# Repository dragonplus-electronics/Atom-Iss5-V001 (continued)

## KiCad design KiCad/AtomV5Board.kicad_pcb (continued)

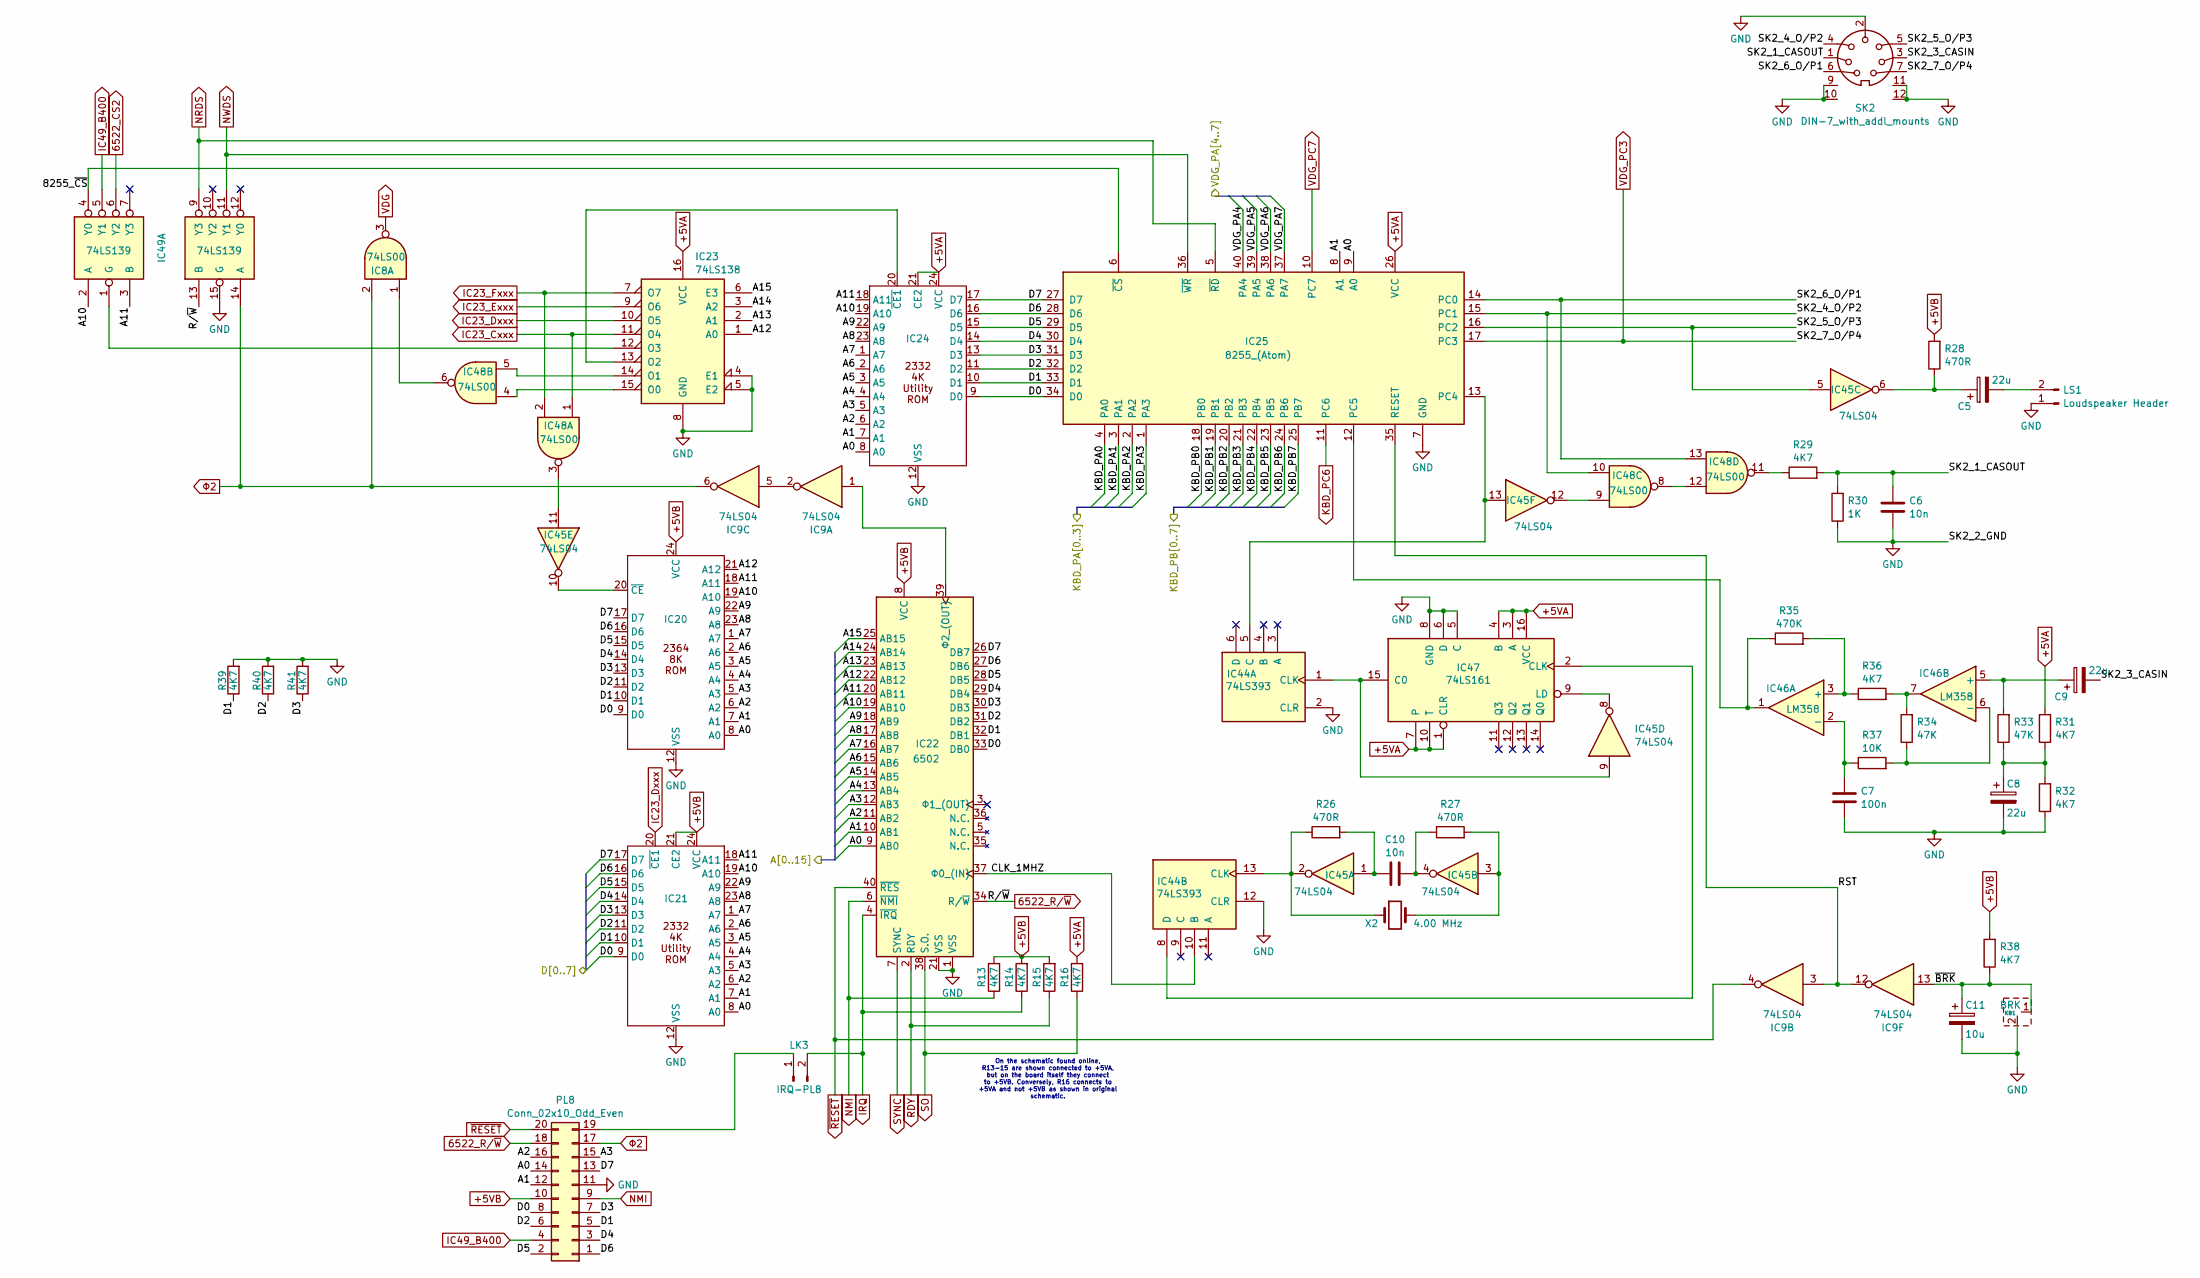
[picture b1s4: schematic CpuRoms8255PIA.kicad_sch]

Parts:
C5: 22u; CP_Radial_LineOnly_P2.54mm_Vertical
C6: 10n; C_Disc_LineOnly_P5.08mm
C7: 100n; C_Disc_LineOnly_P7.62mm
C8: 22u; CP_Axial_LineOnly_P17.78mm_Horizontal
C9: 22u; C_Disc_LineOnly_P5.08mm
C10: 10n; C_Disc_LineOnly_P10.16mm
C11: 10u; CP_Axial_LineOnly_P15.24mm_Horizontal
IC8, IC48: 74LS00; DIP-14_W7.62mm_InnerMarking
IC9, IC45: 74LS04; DIP-14_W7.62mm_InnerMarking
IC20, IC21, IC24: DIP-24_W15.24mm_InnerMarking
IC22: 6502; DIP-40_W15.24mm_InnerMarking
IC23: 74LS138; DIP-16_W7.62mm_InnerMarking
IC25: 8255_(Atom); DIP-40_W15.24mm_InnerMarking
IC44: 74LS393; DIP-14_W7.62mm_InnerMarking
IC46: LM358; DIP-8_W7.62mm_InnerMarking
IC47: 74LS161; DIP-16_W7.62mm_InnerMarking
IC49: 74LS139; DIP-16_W7.62mm_InnerMarking
KB1: BRK; AtomKeyswitch
LK3: IRQ-PL8; PinHeader_1x02_P2.54mm_Vertical
LS1: Loudspeaker Header; PinHeader_1x02_P2.54mm_Vertical
PL8: Conn_02x10_Odd_Even; Atom_IDC-Header_2x10_P2.54mm_Vertical
R13, R14, R15, R16: 4K7; R_Axial_DIN0207_LineOnly_P3.81mm_Vertical
R26, R27, R28: 470R; R_Axial_DIN0207_LineOnly_P2.54mm_Vertical
R29, R39, R40, R41: 4K7; R_Axial_DIN0207_LineOnly_P2.54mm_Vertical
R30: 1K; R_Axial_DIN0207_LineOnly_P2.54mm_Vertical
R31, R32, R36, R38: 4K7; R_Axial_DIN0207_LineOnly_P10.16mm_Horizontal
R33, R34: 47K; R_Axial_DIN0207_LineOnly_P10.16mm_Horizontal
R35: 470K; R_Axial_DIN0207_LineOnly_P10.16mm_Horizontal
R37: 10K; R_Axial_DIN0207_LineOnly_P10.16mm_Horizontal
SK2: DIN-7_with_addl_mounts; DIN-7_RA
X2: 4.00 MHz; C_Disc_LineOnly_P10.16mm

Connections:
6522_CS2: IC49.6 (Y2); also elsewhere on the board
6522_R/~W: IC22.34 (R/~W), IC49.13 (B), PL8.18; also elsewhere on the board
+5VA: IC23.16 (VCC), IC24.21 (CE2), IC24.24 (VCC), IC25.26 (VCC), IC47.1 (CLR), IC47.3 (A), IC47.4 (B), IC47.7, IC47.10 (T), IC47.16 (VCC), R16.2, R31.2; also elsewhere on the board
+5VB: IC20.24 (VCC), IC21.21 (CE2), IC21.24 (VCC), IC22.8 (VCC), PL8.10, R13.2, R14.2, R15.2, R28.2, R38.2; also elsewhere on the board
/6522_PIA & Ports/A0: IC20.8 (A0), IC21.8 (A0), IC22.9 (AB0), IC24.8 (A0), IC25.9 (A0), PL8.14; also elsewhere on the board
/6522_PIA & Ports/A1: IC20.7 (A1), IC21.7 (A1), IC22.10 (AB1), IC24.7 (A1), IC25.8 (A1), PL8.12; also elsewhere on the board
/6522_PIA & Ports/A2: IC20.6 (A2), IC21.6 (A2), IC22.11 (AB2), IC24.6 (A2), PL8.16; also elsewhere on the board
/6522_PIA & Ports/A3: IC20.5 (A3), IC21.5 (A3), IC22.12 (AB3), IC24.5 (A3), PL8.15; also elsewhere on the board
/6522_PIA & Ports/A4: IC20.4 (A4), IC21.4 (A4), IC22.13 (AB4), IC24.4 (A4); also elsewhere on the board
/6522_PIA & Ports/A5: IC20.3 (A5), IC21.3 (A5), IC22.14 (AB5), IC24.3 (A5); also elsewhere on the board
/6522_PIA & Ports/A6: IC20.2 (A6), IC21.2 (A6), IC22.15 (AB6), IC24.2 (A6); also elsewhere on the board
/6522_PIA & Ports/A7: IC20.1 (A7), IC21.1 (A7), IC22.16 (AB7), IC24.1 (A7); also elsewhere on the board
/6522_PIA & Ports/A8: IC20.23 (A8), IC21.23 (A8), IC22.17 (AB8), IC24.23 (A8); also elsewhere on the board
/6522_PIA & Ports/A9: IC20.22 (A9), IC21.22 (A9), IC22.18 (AB9), IC24.22 (A9); also elsewhere on the board
/6522_PIA & Ports/A10: IC20.19 (A10), IC21.19 (A10), IC22.19 (AB10), IC24.19 (A10), IC49.2 (A); also elsewhere on the board
/6522_PIA & Ports/A11: IC20.18 (A11), IC21.18 (A11), IC22.20 (AB11), IC24.18 (A11), IC49.3 (B); also elsewhere on the board
/6522_PIA & Ports/A12: IC20.21 (A12), IC22.22 (AB12), IC23.1 (A0); also elsewhere on the board
/6522_PIA & Ports/A13: IC22.23 (AB13), IC23.2 (A1); also elsewhere on the board
/6522_PIA & Ports/A14: IC22.24 (AB14), IC23.3 (A2); also elsewhere on the board
/6522_PIA & Ports/A15: IC22.25 (AB15), IC23.6 (E3); also elsewhere on the board
/6522_PIA & Ports/D0: IC20.9 (D0), IC21.9 (D0), IC22.33 (DB0), IC24.9 (D0), IC25.34 (D0), PL8.8; also elsewhere on the board
/6522_PIA & Ports/D1: IC20.10 (D1), IC21.10 (D1), IC22.32 (DB1), IC24.10 (D1), IC25.33 (D1), PL8.5, R39.1; also elsewhere on the board
/6522_PIA & Ports/D2: IC20.11 (D2), IC21.11 (D2), IC22.31 (DB2), IC24.11 (D2), IC25.32 (D2), PL8.6, R40.1; also elsewhere on the board
/6522_PIA & Ports/D3: IC20.13 (D3), IC21.13 (D3), IC22.30 (DB3), IC24.13 (D3), IC25.31 (D3), PL8.7, R41.1; also elsewhere on the board
/6522_PIA & Ports/D4: IC20.14 (D4), IC21.14 (D4), IC22.29 (DB4), IC24.14 (D4), IC25.30 (D4), PL8.3; also elsewhere on the board
/6522_PIA & Ports/D5: IC20.15 (D5), IC21.15 (D5), IC22.28 (DB5), IC24.15 (D5), IC25.29 (D5), PL8.2; also elsewhere on the board
/6522_PIA & Ports/D6: IC20.16 (D6), IC21.16 (D6), IC22.27 (DB6), IC24.16 (D6), IC25.28 (D6), PL8.1; also elsewhere on the board
/6522_PIA & Ports/D7: IC20.17 (D7), IC21.17 (D7), IC22.26 (DB7), IC24.17 (D7), IC25.27 (D7), PL8.13; also elsewhere on the board
/CPU, ROMs & 8255 PIA/8255_~CS: IC25.6 (~CS), IC49.4 (Y0)
/CPU, ROMs & 8255 PIA/CLK_1MHZ: IC22.37 (Φ0_(IN)), IC44.10 (B)
/CPU, ROMs & 8255 PIA/KBD_PA0: IC25.4 (PA0); also elsewhere on the board
/CPU, ROMs & 8255 PIA/KBD_PA1: IC25.3 (PA1); also elsewhere on the board
/CPU, ROMs & 8255 PIA/KBD_PA2: IC25.2 (PA2); also elsewhere on the board
/CPU, ROMs & 8255 PIA/KBD_PA3: IC25.1 (PA3); also elsewhere on the board
/CPU, ROMs & 8255 PIA/KBD_PB0: IC25.18 (PB0); also elsewhere on the board
/CPU, ROMs & 8255 PIA/KBD_PB1: IC25.19 (PB1); also elsewhere on the board
/CPU, ROMs & 8255 PIA/KBD_PB2: IC25.20 (PB2); also elsewhere on the board
/CPU, ROMs & 8255 PIA/KBD_PB3: IC25.21 (PB3); also elsewhere on the board
/CPU, ROMs & 8255 PIA/KBD_PB4: IC25.22 (PB4); also elsewhere on the board
/CPU, ROMs & 8255 PIA/KBD_PB5: IC25.23 (PB5); also elsewhere on the board
/CPU, ROMs & 8255 PIA/KBD_PB6: IC25.24 (PB6); also elsewhere on the board
/CPU, ROMs & 8255 PIA/KBD_PB7: IC25.25 (PB7); also elsewhere on the board
/CPU, ROMs & 8255 PIA/RST: IC9.3, IC9.12, IC25.35 (RESET)
/CPU, ROMs & 8255 PIA/SK2_1_CASOUT: C6.1, R29.2, R30.2, SK2.1
/CPU, ROMs & 8255 PIA/SK2_3_CASIN: C9.2, SK2.3
/CPU, ROMs & 8255 PIA/SK2_4_O/P2: IC25.15 (PC1), IC48.10, SK2.4
/CPU, ROMs & 8255 PIA/SK2_5_O/P3: IC25.16 (PC2), IC45.5, SK2.5
/CPU, ROMs & 8255 PIA/SK2_6_O/P1: IC25.14 (PC0), IC48.13, SK2.6
/CPU, ROMs & 8255 PIA/VDG_PA4: IC25.40 (PA4); also elsewhere on the board
/CPU, ROMs & 8255 PIA/VDG_PA5: IC25.39 (PA5); also elsewhere on the board
/CPU, ROMs & 8255 PIA/VDG_PA6: IC25.38 (PA6); also elsewhere on the board
/CPU, ROMs & 8255 PIA/VDG_PA7: IC25.37 (PA7); also elsewhere on the board
/CPU, ROMs & 8255 PIA/~BRK: C11.1, IC9.13, KB1.1, R38.1
GND: C6.2, C7.1, C8.2, C11.2, IC20.12 (VSS), IC21.12 (VSS), IC22.1 (VSS), IC22.21 (VSS), IC23.4 (E1), IC23.5 (E2), IC23.8 (GND), IC24.12 (VSS), IC25.7 (GND), IC44.2 (CLR), IC44.12 (CLR), IC47.5 (C), IC47.6 (D), IC47.8 (GND), IC49.15 (G), KB1.2, LS1.1, PL8.11, R30.1, R32.1, R39.2, R40.2, R41.2, SK2.2, SK2.9, SK2.10, SK2.11, SK2.12; also elsewhere on the board
IC23_Cxxx: IC23.11 (O4), IC48.1
IC23_Dxxx: IC21.20 (~CE1), IC23.10 (O5)
IC23_Exxx: IC23.9 (O6); also elsewhere on the board
IC23_Fxxx: IC23.7 (O7), IC48.2
IC49_B400: IC49.5 (Y1), PL8.4
IRQ: IC22.4 (~IRQ), LK3.2, R14.1; also elsewhere on the board
KBD_PC6: IC25.11 (PC6); also elsewhere on the board
NMI: IC22.6 (~NMI), PL8.9, R13.1; also elsewhere on the board
NRDS: IC25.5 (~RD), IC49.9 (Y3); also elsewhere on the board
NWDS: IC25.36 (~WR), IC49.11 (Y1); also elsewhere on the board
unnamed: C5.1, IC45.6, R28.1
unnamed: C8.1, R31.1, R32.2, R33.1
unnamed: C10.1, IC45.1, R26.2
unnamed: C10.2, IC45.4, R27.1
unnamed: IC9.2, IC9.5
unnamed: IC20.20 (~CE), IC45.10
unnamed: IC9.1, IC22.39 (Φ2_(OUT))
unnamed: IC23.15 (O0), IC48.4
unnamed: IC23.14 (O1), IC48.5
unnamed: IC23.13 (O2), IC24.20 (~CE1)
unnamed: IC23.12 (O3), IC49.1 (G)
unnamed: IC25.13 (PC4), IC44.5 (C), IC45.13
unnamed: IC25.12 (PC5), IC46.1, R35.1
unnamed: IC44.1 (CLK), IC45.9, IC47.15 (C0)
unnamed: IC44.13 (CLK), IC45.2, R26.1, X2.1
unnamed: IC44.8 (D), IC47.2 (CLK)
unnamed: IC45.3, R27.2, X2.2
unnamed: IC45.11, IC48.3
unnamed: IC45.12, IC48.9
unnamed: IC46.7, R34.2, R36.2
unnamed: IC46.3 (+), R35.2, R36.1
unnamed: C7.2, IC46.2 (-), R37.1
unnamed: C9.1, IC46.5 (+), R33.2
unnamed: IC46.6 (-), R34.1, R37.2
unnamed: IC45.8, IC47.9 (LD)
unnamed: IC8.1, IC48.6
unnamed: IC48.11, R29.1
unnamed: IC48.8, IC48.12
unnamed: LK3.1, PL8.19
unnamed: C5.2, LS1.2
RDY: IC22.2 (RDY), R15.1; also elsewhere on the board
SO: IC22.38 (S.O.), R16.1; also elsewhere on the board
SYNC: IC22.7 (SYNC); also elsewhere on the board
VDG: IC8.3; also elsewhere on the board
VDG_PC3: IC25.17 (PC3), SK2.7; also elsewhere on the board
VDG_PC7: IC25.10 (PC7); also elsewhere on the board
~RESET: IC9.4, IC22.40 (~RES), PL8.20; also elsewhere on the board
Φ2: IC8.2, IC9.6, IC49.14 (A), PL8.17; also elsewhere on the board

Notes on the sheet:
On the schematic found online, R13-15 are shown connected to +5VA, but on the board itself they connect to +5VB. Conversely, R16 connects to +5VA and not +5VB as shown in original schematic.

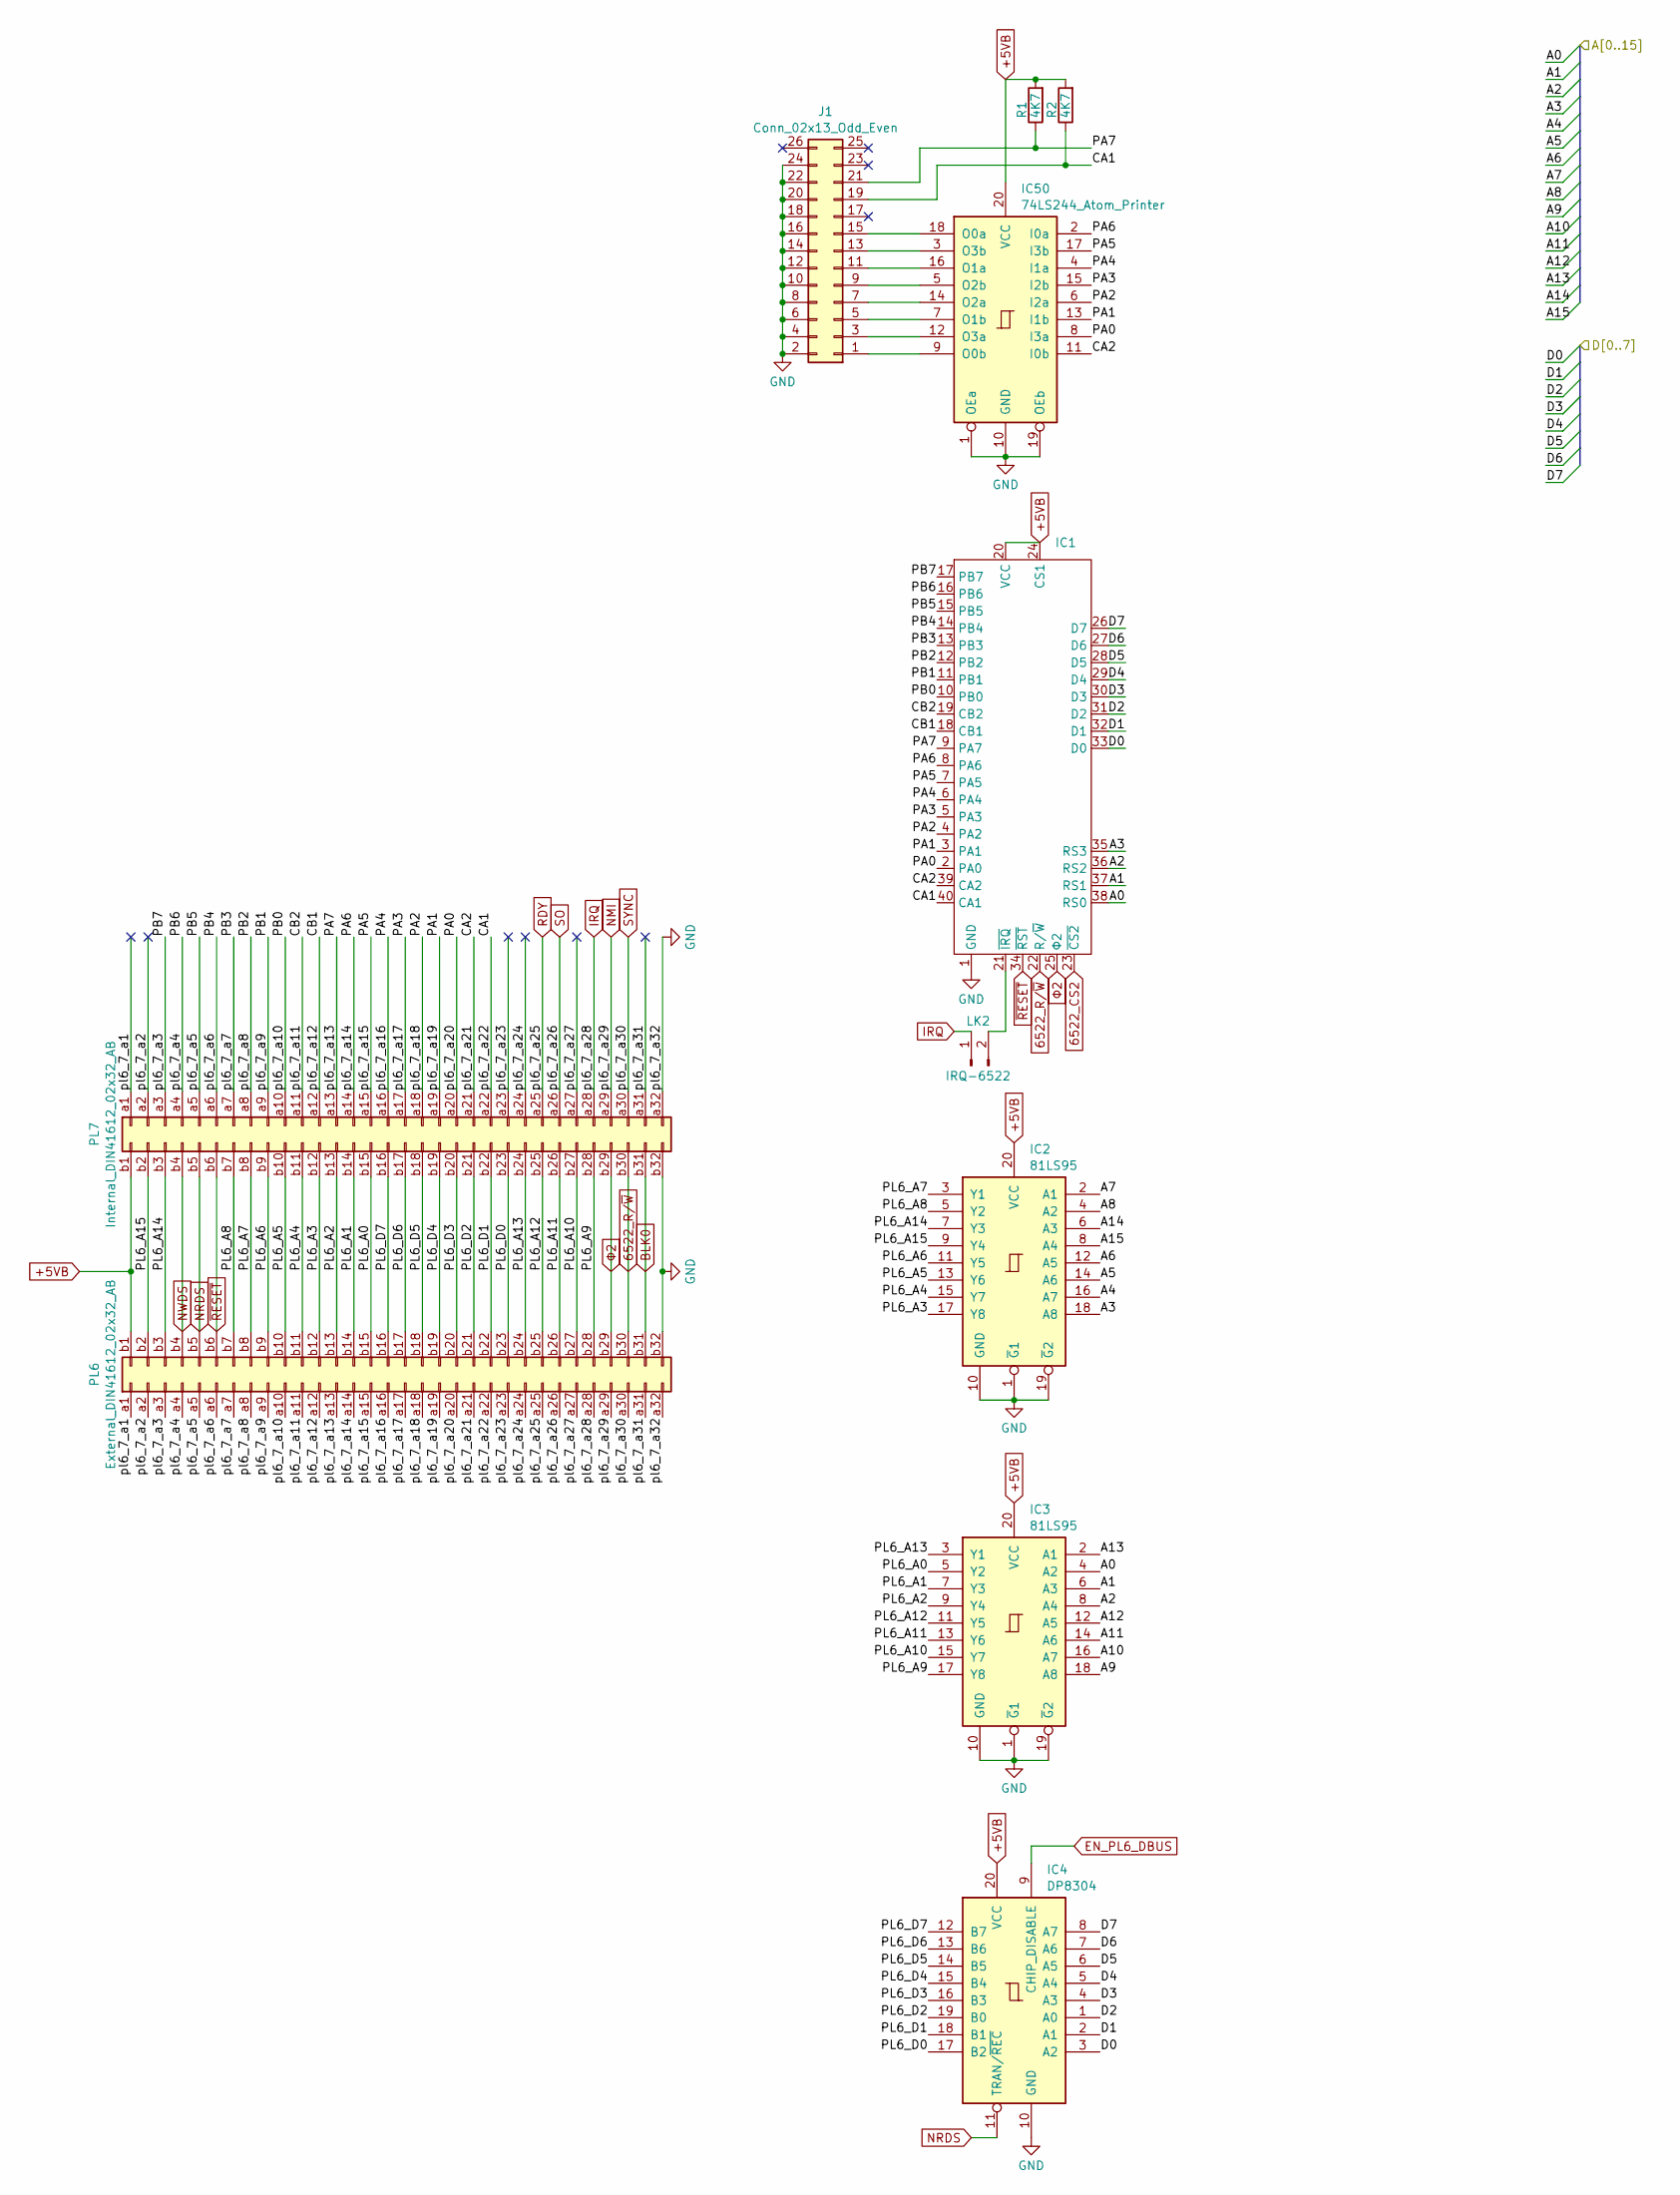
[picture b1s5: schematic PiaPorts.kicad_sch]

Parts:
IC1: DIP-40_W15.24mm_InnerMarking
IC2, IC3: 81LS95; DIP-20_W7.62mm_InnerMarking
IC4: DP8304; DIP-20_W7.62mm_InnerMarking
IC50: 74LS244_Atom_Printer; DIP-20_W7.62mm_InnerMarking
J1: Conn_02x13_Odd_Even; IDC-Header_2x13_P2.54mm_Horizontal
LK2: IRQ-6522; PinHeader_1x02_P2.54mm_Vertical
PL6: External_DIN41612_02x32_AB; DIN41612_B_2x32_Male_Horizontal_THT_NoMountHoles
PL7: Internal_DIN41612_02x32_AB; DIN41612_B_2x32_Female_Vertical_THT
R1, R2: 4K7; R_Axial_DIN0207_LineOnly_P2.54mm_Vertical

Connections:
6522_CS2: IC1.23 (~CS2); also elsewhere on the board
6522_R/~W: IC1.22 (R/~W), PL6.b30, PL7.b30; also elsewhere on the board
+5VB: IC1.20 (VCC), IC1.24 (CS1), IC2.20 (VCC), IC3.20 (VCC), IC4.20 (VCC), IC50.20 (VCC), PL6.b1, PL7.b1, R1.2, R2.2; also elsewhere on the board
/6522_PIA & Ports/A0: IC1.38 (RS0), IC3.4 (A2); also elsewhere on the board
/6522_PIA & Ports/A1: IC1.37 (RS1), IC3.6 (A3); also elsewhere on the board
/6522_PIA & Ports/A2: IC1.36 (RS2), IC3.8 (A4); also elsewhere on the board
/6522_PIA & Ports/A3: IC1.35 (RS3), IC2.18 (A8); also elsewhere on the board
/6522_PIA & Ports/A4: IC2.16 (A7); also elsewhere on the board
/6522_PIA & Ports/A5: IC2.14 (A6); also elsewhere on the board
/6522_PIA & Ports/A6: IC2.12 (A5); also elsewhere on the board
/6522_PIA & Ports/A7: IC2.2 (A1); also elsewhere on the board
/6522_PIA & Ports/A8: IC2.4 (A2); also elsewhere on the board
/6522_PIA & Ports/A9: IC3.18 (A8); also elsewhere on the board
/6522_PIA & Ports/A10: IC3.16 (A7); also elsewhere on the board
/6522_PIA & Ports/A11: IC3.14 (A6); also elsewhere on the board
/6522_PIA & Ports/A12: IC3.12 (A5); also elsewhere on the board
/6522_PIA & Ports/A13: IC3.2 (A1); also elsewhere on the board
/6522_PIA & Ports/A14: IC2.6 (A3); also elsewhere on the board
/6522_PIA & Ports/A15: IC2.8 (A4); also elsewhere on the board
/6522_PIA & Ports/CA1: IC1.40 (CA1), J1.19, PL6.a22, PL7.a22, R2.1
/6522_PIA & Ports/CA2: IC1.39 (CA2), IC50.11 (I0b), PL6.a21, PL7.a21
/6522_PIA & Ports/CB1: IC1.18 (CB1), PL6.a12, PL7.a12
/6522_PIA & Ports/CB2: IC1.19 (CB2), PL6.a11, PL7.a11
/6522_PIA & Ports/D0: IC1.33 (D0), IC4.3 (A2); also elsewhere on the board
/6522_PIA & Ports/D1: IC1.32 (D1), IC4.2 (A1); also elsewhere on the board
/6522_PIA & Ports/D2: IC1.31 (D2), IC4.1 (A0); also elsewhere on the board
/6522_PIA & Ports/D3: IC1.30 (D3), IC4.4 (A3); also elsewhere on the board
/6522_PIA & Ports/D4: IC1.29 (D4), IC4.5 (A4); also elsewhere on the board
/6522_PIA & Ports/D5: IC1.28 (D5), IC4.6 (A5); also elsewhere on the board
/6522_PIA & Ports/D6: IC1.27 (D6), IC4.7 (A6); also elsewhere on the board
/6522_PIA & Ports/D7: IC1.26 (D7), IC4.8 (A7); also elsewhere on the board
/6522_PIA & Ports/PA0: IC1.2 (PA0), IC50.8 (I3a), PL6.a20, PL7.a20
/6522_PIA & Ports/PA1: IC1.3 (PA1), IC50.13 (I1b), PL6.a19, PL7.a19
/6522_PIA & Ports/PA2: IC1.4 (PA2), IC50.6 (I2a), PL6.a18, PL7.a18
/6522_PIA & Ports/PA3: IC1.5 (PA3), IC50.15 (I2b), PL6.a17, PL7.a17
/6522_PIA & Ports/PA4: IC1.6 (PA4), IC50.4 (I1a), PL6.a16, PL7.a16
/6522_PIA & Ports/PA5: IC1.7 (PA5), IC50.17 (I3b), PL6.a15, PL7.a15
/6522_PIA & Ports/PA6: IC1.8 (PA6), IC50.2 (I0a), PL6.a14, PL7.a14
/6522_PIA & Ports/PA7: IC1.9 (PA7), J1.21, PL6.a13, PL7.a13, R1.1
/6522_PIA & Ports/PB0: IC1.10 (PB0), PL6.a10, PL7.a10
/6522_PIA & Ports/PB1: IC1.11 (PB1), PL6.a9, PL7.a9
/6522_PIA & Ports/PB2: IC1.12 (PB2), PL6.a8, PL7.a8
/6522_PIA & Ports/PB3: IC1.13 (PB3), PL6.a7, PL7.a7
/6522_PIA & Ports/PB4: IC1.14 (PB4), PL6.a6, PL7.a6
/6522_PIA & Ports/PB5: IC1.15 (PB5), PL6.a5, PL7.a5
/6522_PIA & Ports/PB6: IC1.16 (PB6), PL6.a4, PL7.a4
/6522_PIA & Ports/PB7: IC1.17 (PB7), PL6.a3, PL7.a3
/6522_PIA & Ports/PL6_A0: IC3.5 (Y2), PL6.b15, PL7.b15
/6522_PIA & Ports/PL6_A1: IC3.7 (Y3), PL6.b14, PL7.b14
/6522_PIA & Ports/PL6_A2: IC3.9 (Y4), PL6.b13, PL7.b13
/6522_PIA & Ports/PL6_A3: IC2.17 (Y8), PL6.b12, PL7.b12
/6522_PIA & Ports/PL6_A4: IC2.15 (Y7), PL6.b11, PL7.b11
/6522_PIA & Ports/PL6_A5: IC2.13 (Y6), PL6.b10, PL7.b10
/6522_PIA & Ports/PL6_A6: IC2.11 (Y5), PL6.b9, PL7.b9
/6522_PIA & Ports/PL6_A7: IC2.3 (Y1), PL6.b8, PL7.b8
/6522_PIA & Ports/PL6_A8: IC2.5 (Y2), PL6.b7, PL7.b7
/6522_PIA & Ports/PL6_A9: IC3.17 (Y8), PL6.b28, PL7.b28
/6522_PIA & Ports/PL6_A10: IC3.15 (Y7), PL6.b27, PL7.b27
/6522_PIA & Ports/PL6_A11: IC3.13 (Y6), PL6.b26, PL7.b26
/6522_PIA & Ports/PL6_A12: IC3.11 (Y5), PL6.b25, PL7.b25
/6522_PIA & Ports/PL6_A13: IC3.3 (Y1), PL6.b24, PL7.b24
/6522_PIA & Ports/PL6_A14: IC2.7 (Y3), PL6.b3, PL7.b3
/6522_PIA & Ports/PL6_A15: IC2.9 (Y4), PL6.b2, PL7.b2
/6522_PIA & Ports/PL6_D0: IC4.17 (B2), PL6.b23, PL7.b23
/6522_PIA & Ports/PL6_D1: IC4.18 (B1), PL6.b22, PL7.b22
/6522_PIA & Ports/PL6_D2: IC4.19 (B0), PL6.b21, PL7.b21
/6522_PIA & Ports/PL6_D3: IC4.16 (B3), PL6.b20, PL7.b20
/6522_PIA & Ports/PL6_D4: IC4.15 (B4), PL6.b19, PL7.b19
/6522_PIA & Ports/PL6_D5: IC4.14 (B5), PL6.b18, PL7.b18
/6522_PIA & Ports/PL6_D6: IC4.13 (B6), PL6.b17, PL7.b17
/6522_PIA & Ports/PL6_D7: IC4.12 (B7), PL6.b16, PL7.b16
/6522_PIA & Ports/pl6_7_a1: PL6.a1, PL7.a1
/6522_PIA & Ports/pl6_7_a2: PL6.a2, PL7.a2
/6522_PIA & Ports/pl6_7_a23: PL6.a23, PL7.a23
/6522_PIA & Ports/pl6_7_a24: PL6.a24, PL7.a24
/6522_PIA & Ports/pl6_7_a27: PL6.a27, PL7.a27
/6522_PIA & Ports/pl6_7_a31: PL6.a31, PL7.a31
BLK0: PL6.b31, PL7.b31; also elsewhere on the board
EN_PL6_DBUS: IC4.9 (CHIP_DISABLE); also elsewhere on the board
GND: IC1.1 (GND), IC2.1 (~G1), IC2.10 (GND), IC2.19 (~G2), IC3.1 (~G1), IC3.10 (GND), IC3.19 (~G2), IC4.10 (GND), IC50.1 (OEa), IC50.10 (GND), IC50.19 (OEb), J1.2, J1.4, J1.6, J1.8, J1.10, J1.12, J1.14, J1.16, J1.18, J1.20, J1.22, J1.24, PL6.a32, PL6.b32, PL7.a32, PL7.b32; also elsewhere on the board
IRQ: LK2.1, PL6.a28, PL7.a28; also elsewhere on the board
NMI: PL6.a29, PL7.a29; also elsewhere on the board
NRDS: IC4.11 (TRAN/~REC), PL6.b5, PL7.b5; also elsewhere on the board
NWDS: PL6.b4, PL7.b4; also elsewhere on the board
unnamed: IC1.21 (~IRQ), LK2.2
unnamed: IC50.18 (O0a), J1.15
unnamed: IC50.9 (O0b), J1.1
unnamed: IC50.16 (O1a), J1.11
unnamed: IC50.7 (O1b), J1.5
unnamed: IC50.14 (O2a), J1.7
unnamed: IC50.5 (O2b), J1.9
unnamed: IC50.12 (O3a), J1.3
unnamed: IC50.3 (O3b), J1.13
RDY: PL6.a25, PL7.a25; also elsewhere on the board
SO: PL6.a26, PL7.a26; also elsewhere on the board
SYNC: PL6.a30, PL7.a30; also elsewhere on the board
~RESET: IC1.34 (~RST), PL6.b6, PL7.b6; also elsewhere on the board
Φ2: IC1.25 (Φ2), PL6.b29, PL7.b29; also elsewhere on the board

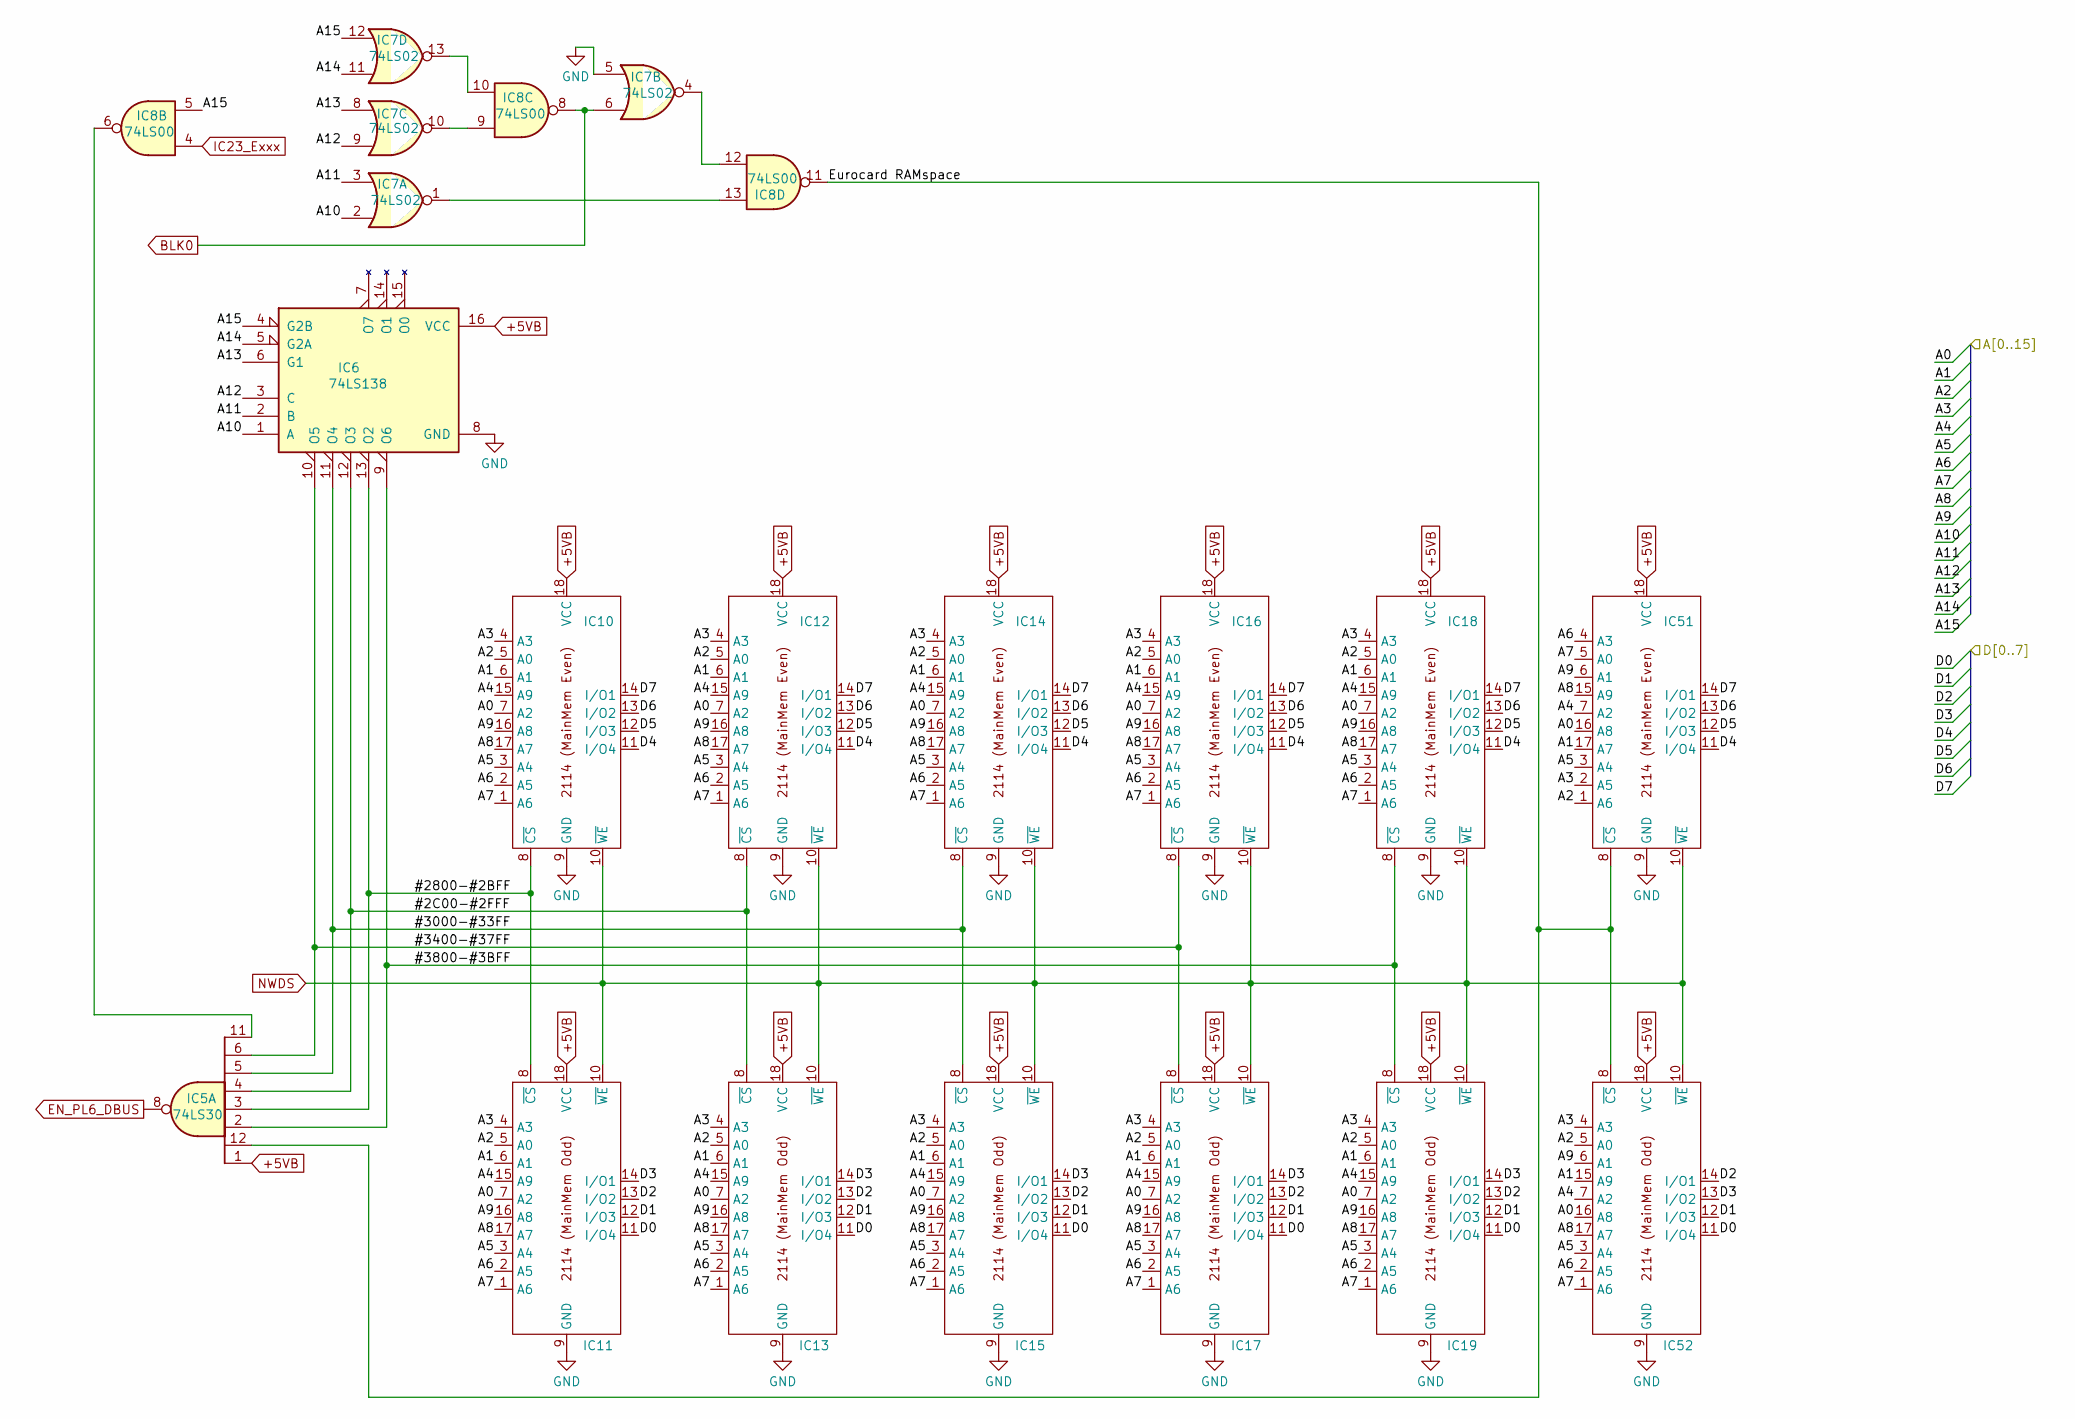
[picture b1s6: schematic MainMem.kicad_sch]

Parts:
IC5: 74LS30; DIP-14_W7.62mm_InnerMarking
IC6: 74LS138; DIP-16_W7.62mm_InnerMarking
IC7: 74LS02; DIP-14_W7.62mm_InnerMarking
IC8: 74LS00; DIP-14_W7.62mm_InnerMarking
IC10, IC12, IC14, IC16, IC18, IC51: 2114; DIP-18_W7.62mm_InnerMarking
IC11, IC13, IC15, IC17, IC19, IC52: DIP-18_W7.62mm_InnerMarking

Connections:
+5VB: IC5.1, IC6.16 (VCC), IC10.18 (VCC), IC11.18 (VCC), IC12.18 (VCC), IC13.18 (VCC), IC14.18 (VCC), IC15.18 (VCC), IC16.18 (VCC), IC17.18 (VCC), IC18.18 (VCC), IC19.18 (VCC), IC51.18 (VCC), IC52.18 (VCC); also elsewhere on the board
/6522_PIA & Ports/A0: IC10.7 (A2), IC11.7 (A2), IC12.7 (A2), IC13.7 (A2), IC14.7 (A2), IC15.7 (A2), IC16.7 (A2), IC17.7 (A2), IC18.7 (A2), IC19.7 (A2), IC51.16 (A8), IC52.16 (A8); also elsewhere on the board
/6522_PIA & Ports/A1: IC10.6 (A1), IC11.6 (A1), IC12.6 (A1), IC13.6 (A1), IC14.6 (A1), IC15.6 (A1), IC16.6 (A1), IC17.6 (A1), IC18.6 (A1), IC19.6 (A1), IC51.17 (A7), IC52.15 (A9); also elsewhere on the board
/6522_PIA & Ports/A2: IC10.5 (A0), IC11.5 (A0), IC12.5 (A0), IC13.5 (A0), IC14.5 (A0), IC15.5 (A0), IC16.5 (A0), IC17.5 (A0), IC18.5 (A0), IC19.5 (A0), IC51.1 (A6), IC52.5 (A0); also elsewhere on the board
/6522_PIA & Ports/A3: IC10.4 (A3), IC11.4 (A3), IC12.4 (A3), IC13.4 (A3), IC14.4 (A3), IC15.4 (A3), IC16.4 (A3), IC17.4 (A3), IC18.4 (A3), IC19.4 (A3), IC51.2 (A5), IC52.4 (A3); also elsewhere on the board
/6522_PIA & Ports/A4: IC10.15 (A9), IC11.15 (A9), IC12.15 (A9), IC13.15 (A9), IC14.15 (A9), IC15.15 (A9), IC16.15 (A9), IC17.15 (A9), IC18.15 (A9), IC19.15 (A9), IC51.7 (A2), IC52.7 (A2); also elsewhere on the board
/6522_PIA & Ports/A5: IC10.3 (A4), IC11.3 (A4), IC12.3 (A4), IC13.3 (A4), IC14.3 (A4), IC15.3 (A4), IC16.3 (A4), IC17.3 (A4), IC18.3 (A4), IC19.3 (A4), IC51.3 (A4), IC52.3 (A4); also elsewhere on the board
/6522_PIA & Ports/A6: IC10.2 (A5), IC11.2 (A5), IC12.2 (A5), IC13.2 (A5), IC14.2 (A5), IC15.2 (A5), IC16.2 (A5), IC17.2 (A5), IC18.2 (A5), IC19.2 (A5), IC51.4 (A3), IC52.2 (A5); also elsewhere on the board
/6522_PIA & Ports/A7: IC10.1 (A6), IC11.1 (A6), IC12.1 (A6), IC13.1 (A6), IC14.1 (A6), IC15.1 (A6), IC16.1 (A6), IC17.1 (A6), IC18.1 (A6), IC19.1 (A6), IC51.5 (A0), IC52.1 (A6); also elsewhere on the board
/6522_PIA & Ports/A8: IC10.17 (A7), IC11.17 (A7), IC12.17 (A7), IC13.17 (A7), IC14.17 (A7), IC15.17 (A7), IC16.17 (A7), IC17.17 (A7), IC18.17 (A7), IC19.17 (A7), IC51.15 (A9), IC52.17 (A7); also elsewhere on the board
/6522_PIA & Ports/A9: IC10.16 (A8), IC11.16 (A8), IC12.16 (A8), IC13.16 (A8), IC14.16 (A8), IC15.16 (A8), IC16.16 (A8), IC17.16 (A8), IC18.16 (A8), IC19.16 (A8), IC51.6 (A1), IC52.6 (A1); also elsewhere on the board
/6522_PIA & Ports/A10: IC6.1 (A), IC7.2; also elsewhere on the board
/6522_PIA & Ports/A11: IC6.2 (B), IC7.3; also elsewhere on the board
/6522_PIA & Ports/A12: IC6.3 (C), IC7.9; also elsewhere on the board
/6522_PIA & Ports/A13: IC6.6 (G1), IC7.8; also elsewhere on the board
/6522_PIA & Ports/A14: IC6.5 (G2A), IC7.11; also elsewhere on the board
/6522_PIA & Ports/A15: IC6.4 (G2B), IC7.12, IC8.5; also elsewhere on the board
/6522_PIA & Ports/D0: IC11.11 (I/O4), IC13.11 (I/O4), IC15.11 (I/O4), IC17.11 (I/O4), IC19.11 (I/O4), IC52.11 (I/O4); also elsewhere on the board
/6522_PIA & Ports/D1: IC11.12 (I/O3), IC13.12 (I/O3), IC15.12 (I/O3), IC17.12 (I/O3), IC19.12 (I/O3), IC52.12 (I/O3); also elsewhere on the board
/6522_PIA & Ports/D2: IC11.13 (I/O2), IC13.13 (I/O2), IC15.13 (I/O2), IC17.13 (I/O2), IC19.13 (I/O2), IC52.14 (I/O1); also elsewhere on the board
/6522_PIA & Ports/D3: IC11.14 (I/O1), IC13.14 (I/O1), IC15.14 (I/O1), IC17.14 (I/O1), IC19.14 (I/O1), IC52.13 (I/O2); also elsewhere on the board
/6522_PIA & Ports/D4: IC10.11 (I/O4), IC12.11 (I/O4), IC14.11 (I/O4), IC16.11 (I/O4), IC18.11 (I/O4), IC51.11 (I/O4); also elsewhere on the board
/6522_PIA & Ports/D5: IC10.12 (I/O3), IC12.12 (I/O3), IC14.12 (I/O3), IC16.12 (I/O3), IC18.12 (I/O3), IC51.12 (I/O3); also elsewhere on the board
/6522_PIA & Ports/D6: IC10.13 (I/O2), IC12.13 (I/O2), IC14.13 (I/O2), IC16.13 (I/O2), IC18.13 (I/O2), IC51.13 (I/O2); also elsewhere on the board
/6522_PIA & Ports/D7: IC10.14 (I/O1), IC12.14 (I/O1), IC14.14 (I/O1), IC16.14 (I/O1), IC18.14 (I/O1), IC51.14 (I/O1); also elsewhere on the board
/MainMemory/#2C00-#2FFF: IC5.4, IC6.12 (O3), IC12.8 (~CS), IC13.8 (~CS)
/MainMemory/#2800-#2BFF: IC5.3, IC6.13 (O2), IC10.8 (~CS), IC11.8 (~CS)
/MainMemory/#3000-#33FF: IC5.5, IC6.11 (O4), IC14.8 (~CS), IC15.8 (~CS)
/MainMemory/#3400-#37FF: IC5.6, IC6.10 (O5), IC16.8 (~CS), IC17.8 (~CS)
/MainMemory/#3800-#3BFF: IC5.2, IC6.9 (O6), IC18.8 (~CS), IC19.8 (~CS)
/MainMemory/Eurocard RAMspace: IC5.12, IC8.11, IC51.8 (~CS), IC52.8 (~CS)
BLK0: IC7.6, IC8.8; also elsewhere on the board
EN_PL6_DBUS: IC5.8; also elsewhere on the board
GND: IC6.8 (GND), IC7.5, IC10.9 (GND), IC11.9 (GND), IC12.9 (GND), IC13.9 (GND), IC14.9 (GND), IC15.9 (GND), IC16.9 (GND), IC17.9 (GND), IC18.9 (GND), IC19.9 (GND), IC51.9 (GND), IC52.9 (GND); also elsewhere on the board
IC23_Exxx: IC8.4; also elsewhere on the board
NWDS: IC10.10 (~WE), IC11.10 (~WE), IC12.10 (~WE), IC13.10 (~WE), IC14.10 (~WE), IC15.10 (~WE), IC16.10 (~WE), IC17.10 (~WE), IC18.10 (~WE), IC19.10 (~WE), IC51.10 (~WE), IC52.10 (~WE); also elsewhere on the board
unnamed: IC5.11, IC8.6
unnamed: IC7.1, IC8.13
unnamed: IC7.4, IC8.12
unnamed: IC7.10, IC8.9
unnamed: IC7.13, IC8.10
